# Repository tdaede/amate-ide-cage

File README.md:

This is a PCB for the NEC PC-9821 A-Mate series hard drive caddies, e.g. the NEC PC-9821A-E07 or ICM INTER-340A.

The PCB is mechanically compatible, though note that the IDE cable is reversed comapred to the NEC board! NEC uses a ribbon cable with the connector crimped on backwards. This PCB is instead marked for a standard, straight through IDE cable. The connector can still be installed reversed if desired, or a right angle connector could be used for e.g. a CF card adapter.

Also note that the 74HCT157s are in a narrow SO package rather than the more common SOIC.

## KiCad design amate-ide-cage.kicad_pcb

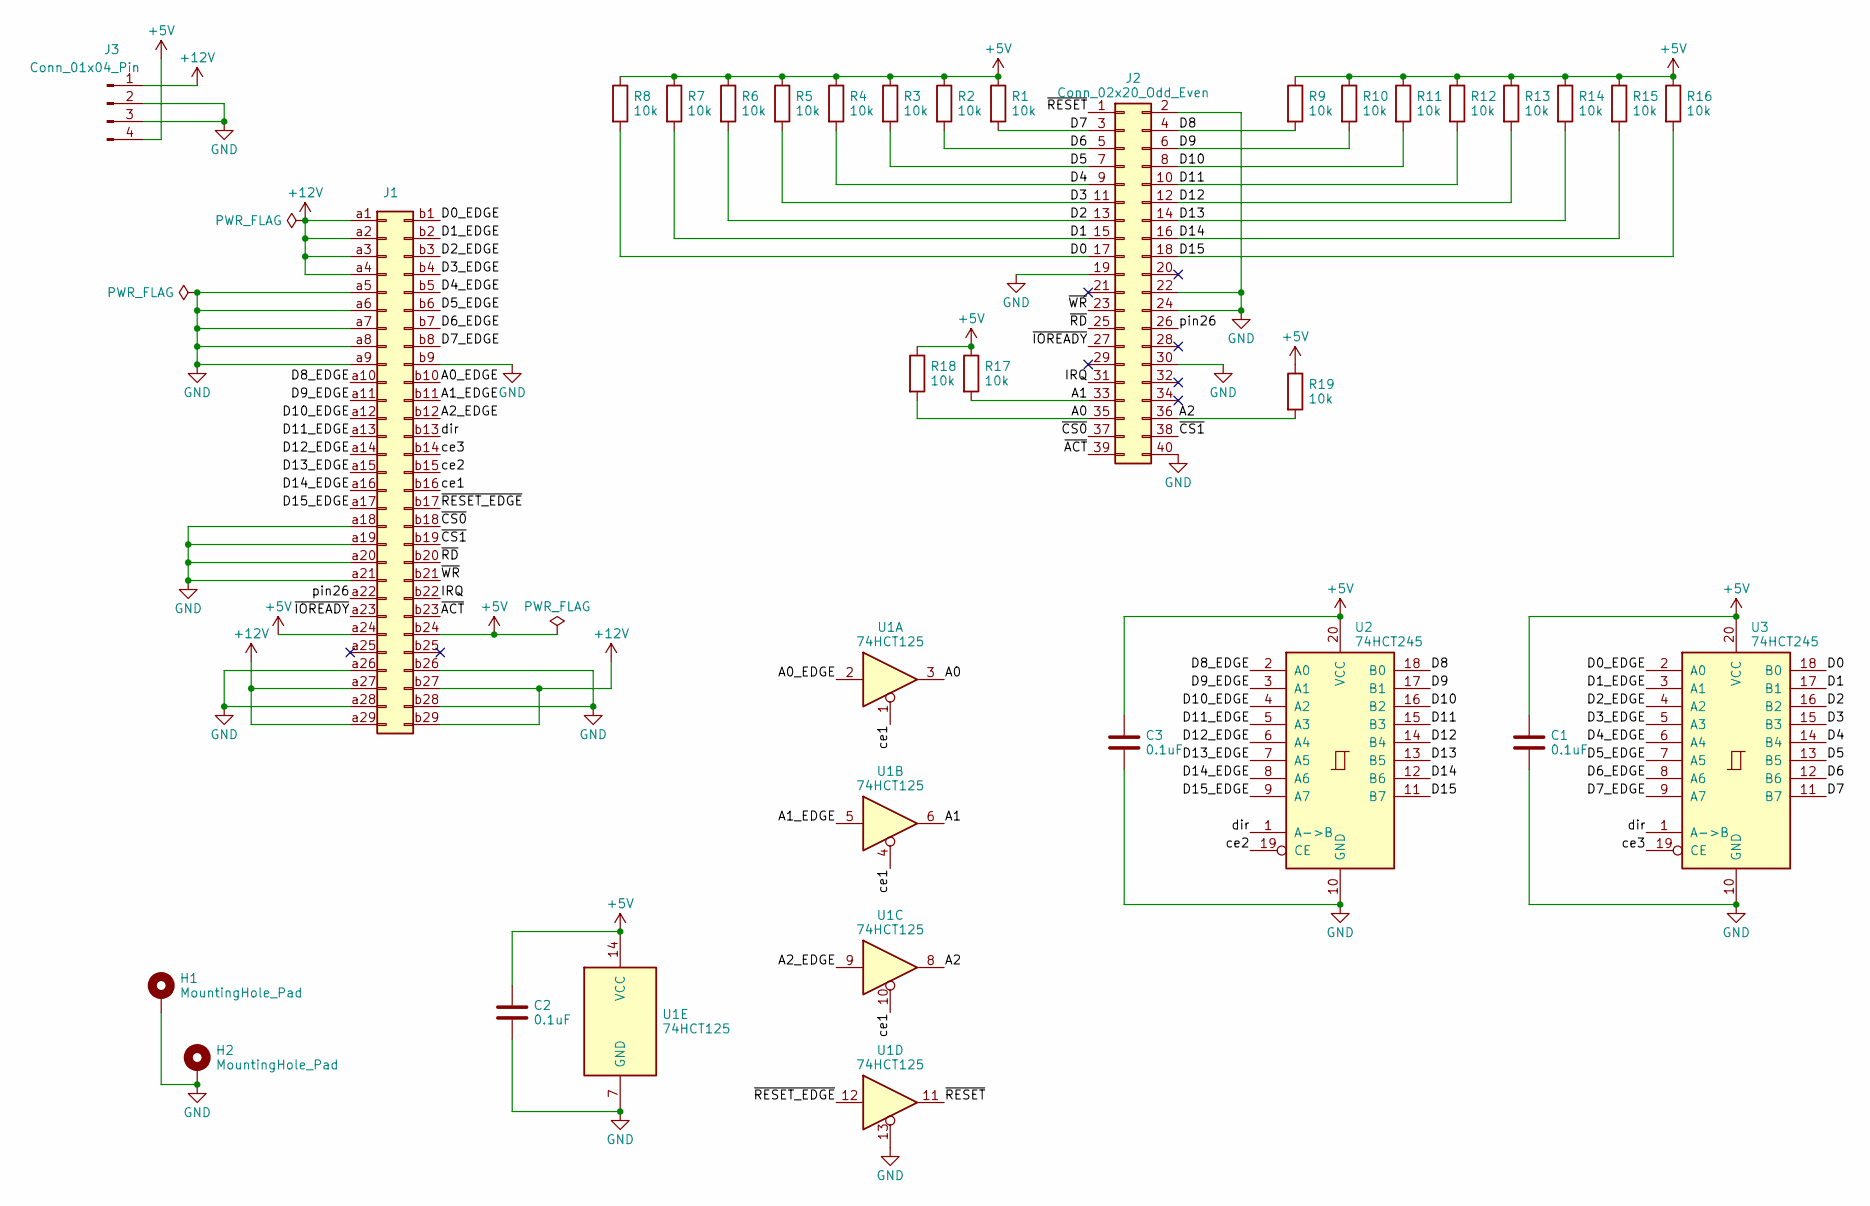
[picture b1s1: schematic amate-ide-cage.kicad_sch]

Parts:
C1, C2, C3: 0.1uF; C_0603_1608Metric; Digikey 311-1341-1-ND
H1, H2: MountingHole_Pad; MountingHole_3mm_Pad; Digikey DNP
J1: amate_ide_edge; Digikey DNP
J2: Conn_02x20_Odd_Even; IDC-Header_2x20_P2.54mm_Vertical; Digikey S9175-ND
J3: Conn_01x04_Pin; Molex_KK-396_5273-04A_1x04_P3.96mm_Vertical; Digikey WM4622-ND
R1, R2, R3, R4, R5, R6, R7, R8, R9, R10, R11, R12, R13, R14, R15, R16, R17, R18, R19: 10k; R_0603_1608Metric; Digikey 311-10.0KHRCT-ND
U1: 74HCT125; SOIC-14_3.9x8.7mm_P1.27mm; Digikey 1727-2834-1-ND
U2, U3: 74HCT245; SO-20_5.3x12.6mm_P1.27mm; Digikey 296-15849-1-ND

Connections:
+5V: C1.1, C2.1, C3.1, J1.a24, J1.b24, J3.4, R1.1, R2.1, R3.1, R4.1, R5.1, R6.1, R7.1, R8.1, R9.1, R10.1, R11.1, R12.1, R13.1, R14.1, R15.1, R16.1, R17.1, R18.1, R19.1, U1.14 (VCC), U2.20 (VCC), U3.20 (VCC)
+12V: J1.a1, J1.a2, J1.a3, J1.a4, J1.a27, J1.a29, J1.b27, J1.b29, J3.1
/A0: J2.35, R18.2, U1.3
/A0_EDGE: J1.b10, U1.2
/A1: J2.33, R17.2, U1.6
/A1_EDGE: J1.b11, U1.5
/A2: J2.36, R19.2, U1.8
/A2_EDGE: J1.b12, U1.9
/D0: J2.17, R8.2, U3.18 (B0)
/D0_EDGE: J1.b1, U3.2 (A0)
/D1: J2.15, R7.2, U3.17 (B1)
/D1_EDGE: J1.b2, U3.3 (A1)
/D2: J2.13, R6.2, U3.16 (B2)
/D2_EDGE: J1.b3, U3.4 (A2)
/D3: J2.11, R5.2, U3.15 (B3)
/D3_EDGE: J1.b4, U3.5 (A3)
/D4: J2.9, R4.2, U3.14 (B4)
/D4_EDGE: J1.b5, U3.6 (A4)
/D5: J2.7, R3.2, U3.13 (B5)
/D5_EDGE: J1.b6, U3.7 (A5)
/D6: J2.5, R2.2, U3.12 (B6)
/D6_EDGE: J1.b7, U3.8 (A6)
/D7: J2.3, R1.2, U3.11 (B7)
/D7_EDGE: J1.b8, U3.9 (A7)
/D8: J2.4, R9.2, U2.18 (B0)
/D8_EDGE: J1.a10, U2.2 (A0)
/D9: J2.6, R10.2, U2.17 (B1)
/D9_EDGE: J1.a11, U2.3 (A1)
/D10: J2.8, R11.2, U2.16 (B2)
/D10_EDGE: J1.a12, U2.4 (A2)
/D11: J2.10, R12.2, U2.15 (B3)
/D11_EDGE: J1.a13, U2.5 (A3)
/D12: J2.12, R13.2, U2.14 (B4)
/D12_EDGE: J1.a14, U2.6 (A4)
/D13: J2.14, R14.2, U2.13 (B5)
/D13_EDGE: J1.a15, U2.7 (A5)
/D14: J2.16, R15.2, U2.12 (B6)
/D14_EDGE: J1.a16, U2.8 (A6)
/D15: J2.18, R16.2, U2.11 (B7)
/D15_EDGE: J1.a17, U2.9 (A7)
/IRQ: J1.b22, J2.31
/ce1: J1.b16, U1.1, U1.4, U1.10
/ce2: J1.b15, U2.19 (CE)
/ce3: J1.b14, U3.19 (CE)
/dir: J1.b13, U2.1 (A->B), U3.1 (A->B)
/pin26: J1.a22, J2.26
/~ACT: J1.b23, J2.39
/~CS0: J1.b18, J2.37
/~CS1: J1.b19, J2.38
/~IOREADY: J1.a23, J2.27
/~RD: J1.b20, J2.25
/~RESET_EDGE: J1.b17, U1.12
/~RESET: J2.1, U1.11
/~WR: J1.b21, J2.23
GND: C1.2, C2.2, C3.2, H1.1, H2.1, J1.a5, J1.a6, J1.a7, J1.a8, J1.a9, J1.a18, J1.a19, J1.a20, J1.a21, J1.a26, J1.a28, J1.b9, J1.b26, J1.b28, J2.2, J2.19, J2.22, J2.24, J2.30, J2.40, J3.2, J3.3, U1.7 (GND), U1.13, U2.10 (GND), U3.10 (GND)

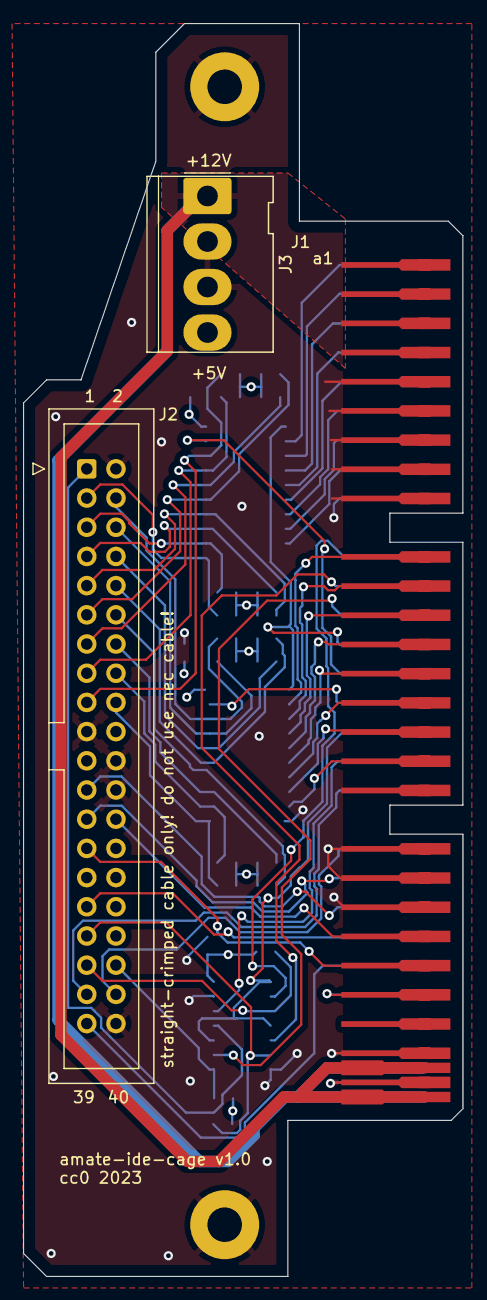
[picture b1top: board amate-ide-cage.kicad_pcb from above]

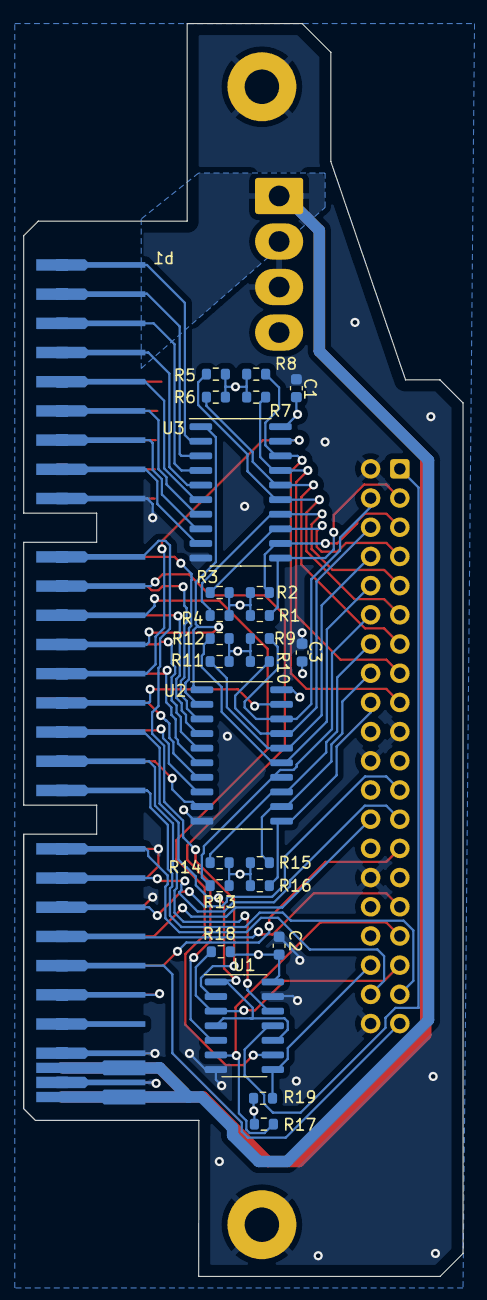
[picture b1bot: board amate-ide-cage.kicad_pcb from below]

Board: 4 copper layers, 38.2 x 109.0 mm, 30 parts (25 on the bottom side), 55 nets.
